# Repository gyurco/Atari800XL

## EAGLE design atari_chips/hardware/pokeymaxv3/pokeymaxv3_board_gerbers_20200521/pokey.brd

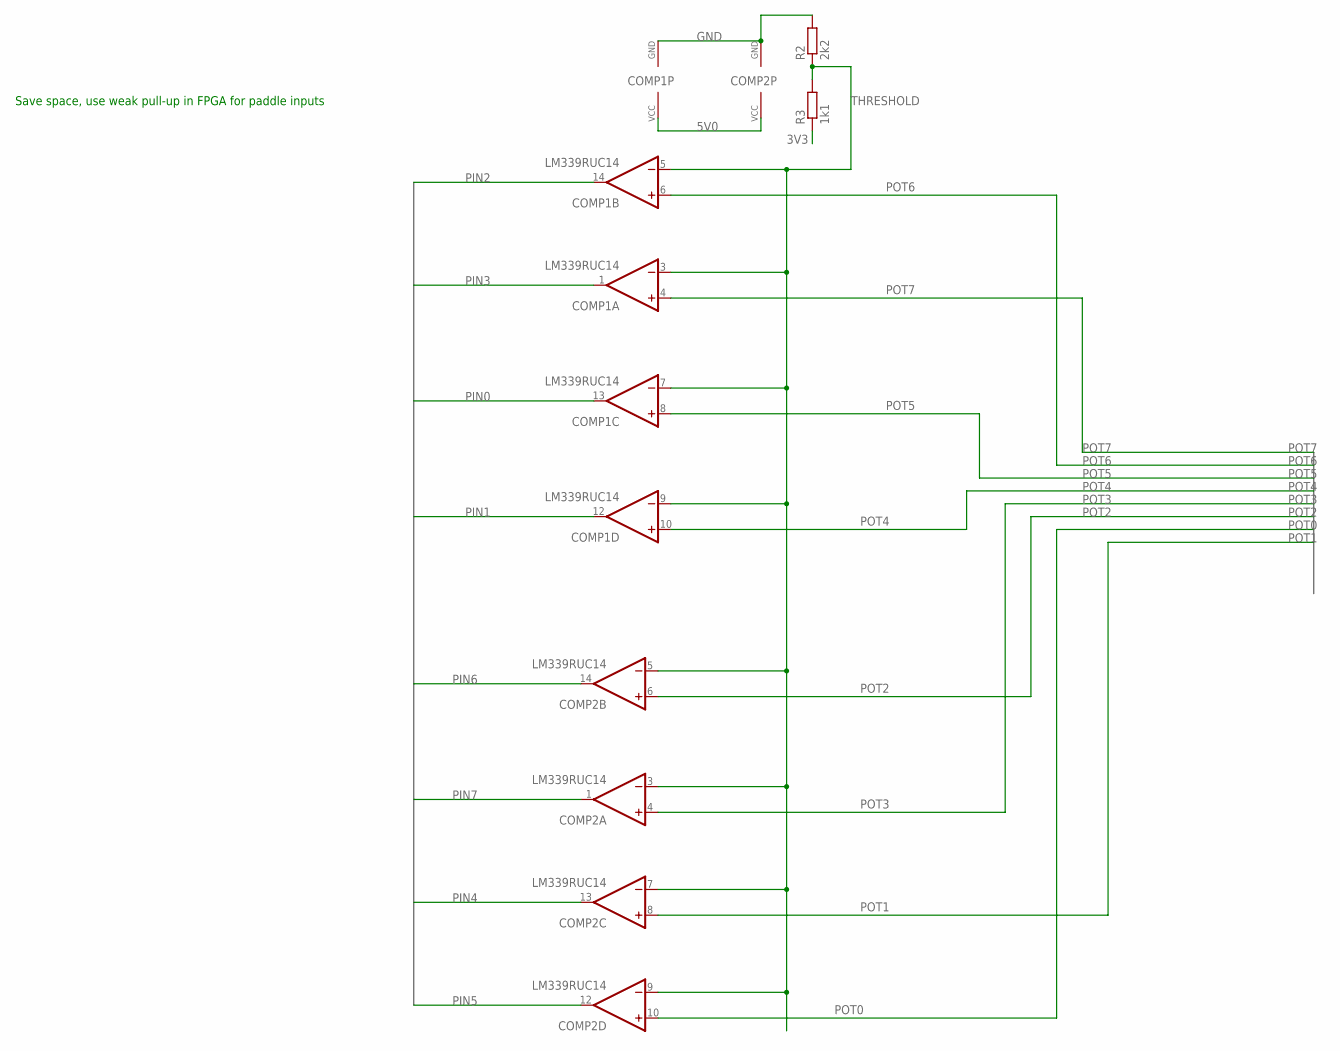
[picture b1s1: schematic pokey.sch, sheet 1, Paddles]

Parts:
COMP1, COMP2: LM339RUC14; RUC14
R2: 2k2; R0402
R3: 1k1; R0402

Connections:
3V3: R3.1; also elsewhere on the board
5V0: COMP1.2 (VCC), COMP2.2 (VCC); also elsewhere on the board
GND: COMP1.11 (GND), COMP2.11 (GND), R2.2; also elsewhere on the board
PIN0: COMP1.13 (OUT); also elsewhere on the board
PIN1: COMP1.12 (OUT); also elsewhere on the board
PIN2: COMP1.14 (OUT); also elsewhere on the board
PIN3: COMP1.1 (OUT); also elsewhere on the board
PIN4: COMP2.13 (OUT); also elsewhere on the board
PIN5: COMP2.12 (OUT); also elsewhere on the board
PIN6: COMP2.14 (OUT); also elsewhere on the board
PIN7: COMP2.1 (OUT); also elsewhere on the board
POT0: COMP2.10 (+IN); also elsewhere on the board
POT1: COMP2.8 (+IN); also elsewhere on the board
POT2: COMP2.6 (+IN); also elsewhere on the board
POT3: COMP2.4 (+IN); also elsewhere on the board
POT4: COMP1.10 (+IN); also elsewhere on the board
POT5: COMP1.8 (+IN); also elsewhere on the board
POT6: COMP1.6 (+IN); also elsewhere on the board
POT7: COMP1.4 (+IN); also elsewhere on the board
THRESHOLD: COMP1.3 (-IN), COMP1.5 (-IN), COMP1.7 (-IN), COMP1.9 (-IN), COMP2.3 (-IN), COMP2.5 (-IN), COMP2.7 (-IN), COMP2.9 (-IN), R2.1, R3.2

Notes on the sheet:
Save space, use weak pull-up in FPGA for paddle inputs

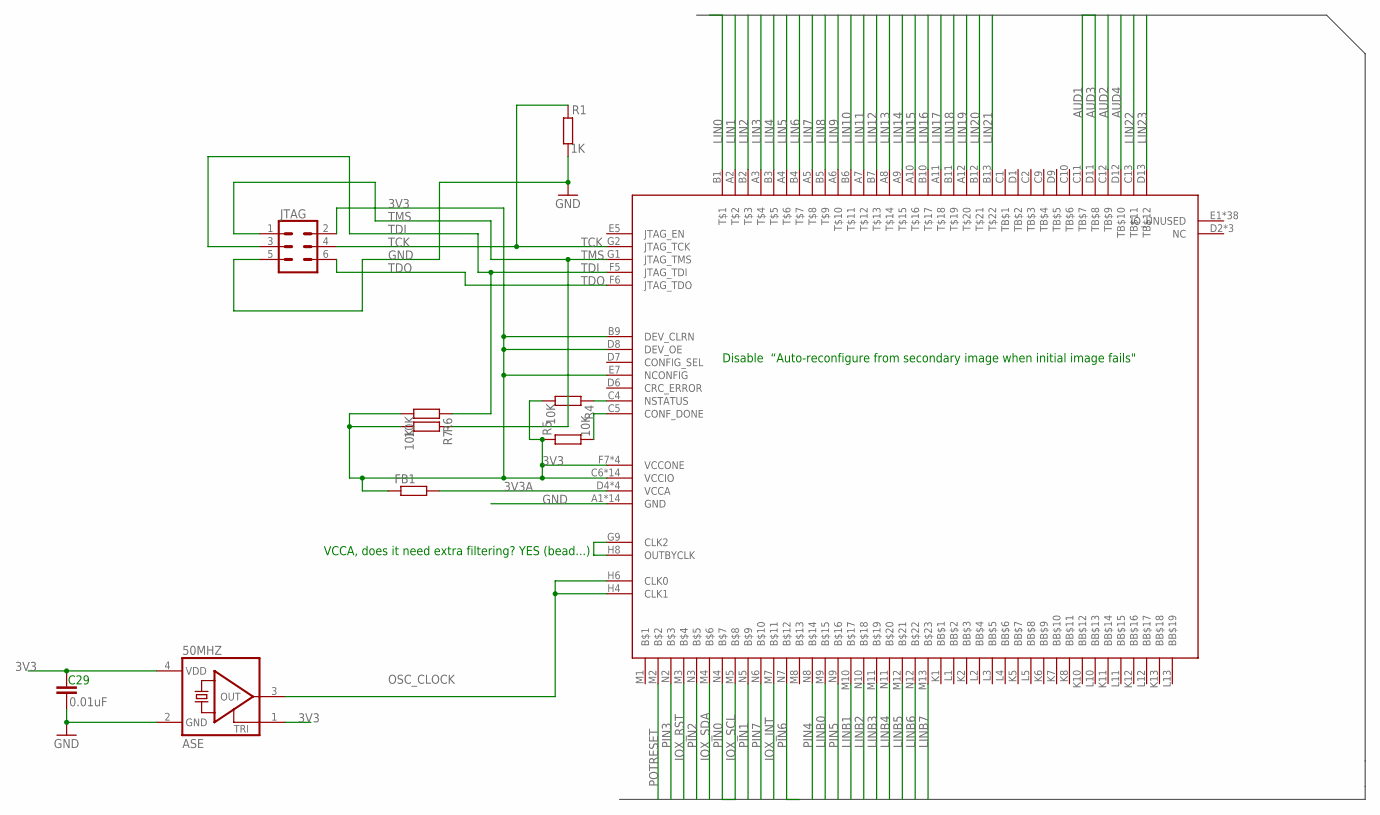
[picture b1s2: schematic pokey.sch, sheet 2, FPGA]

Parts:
50MHZ: ASE
C29: 0.01uF; C0402
FB1: R-EU_R0402; R0402
JTAG: CONN_03X2LOCK; 2X3_LOCK
MAX10: MAX10; U169SMALL
R1: 1K; R0402
R4, R5, R6, R7: 10K; R0402

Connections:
3V3: 50MHZ.1 (TRI), 50MHZ.4 (VDD), C29.1, FB1.1, JTAG.2, MAX10.B9 (DEV_CLRN), MAX10.C6 (VCCIO), MAX10.C7 (VCCIO), MAX10.C8 (VCCIO), MAX10.D8 (DEV_OE), MAX10.E7 (NCONFIG), MAX10.F2 (VCCIO), MAX10.F7 (VCCONE), MAX10.F11 (VCCIO), MAX10.G3 (VCCIO), MAX10.G6 (VCCONE), MAX10.G8 (VCCONE), MAX10.G11 (VCCIO), MAX10.H7 (VCCONE), MAX10.H11 (VCCIO), MAX10.J3 (VCCIO), MAX10.J11 (VCCIO), MAX10.K3 (VCCIO), MAX10.L6 (VCCIO), MAX10.L7 (VCCIO), MAX10.L8 (VCCIO), R4.2, R5.1, R6.2, R7.2; also elsewhere on the board
3V3A: FB1.2, MAX10.D4 (VCCA), MAX10.D10 (VCCA), MAX10.K4 (VCCA), MAX10.K9 (VCCA); also elsewhere on the board
AUD1: MAX10.C11 (TB$7); also elsewhere on the board
AUD2: MAX10.C12 (TB$9); also elsewhere on the board
AUD3: MAX10.D11 (TB$8); also elsewhere on the board
AUD4: MAX10.D12 (TB$10); also elsewhere on the board
CONF_DONE: MAX10.C5 (CONF_DONE), R5.2
FAKE_CLK: MAX10.G9 (CLK2), MAX10.H8 (OUTBYCLK)
GND: 50MHZ.2 (GND), C29.2, JTAG.5, MAX10.A1 (GND), MAX10.A13 (GND), MAX10.B8 (GND), MAX10.C3 (GND), MAX10.D5 (GND), MAX10.E11 (GND), MAX10.F3 (GND), MAX10.G7 (GND), MAX10.H12 (GND), MAX10.J4 (GND), MAX10.L9 (GND), MAX10.M6 (GND), MAX10.N1 (GND), MAX10.N13 (GND), R1.2; also elsewhere on the board
IOX_INT: MAX10.M7; also elsewhere on the board
IOX_RST: MAX10.M3; also elsewhere on the board
IOX_SCL: MAX10.M5; also elsewhere on the board
IOX_SDA: MAX10.M4; also elsewhere on the board
LIN0: MAX10.B1; also elsewhere on the board
LIN1: MAX10.A2; also elsewhere on the board
LIN2: MAX10.B2; also elsewhere on the board
LIN3: MAX10.A3; also elsewhere on the board
LIN4: MAX10.B3; also elsewhere on the board
LIN5: MAX10.A4; also elsewhere on the board
LIN6: MAX10.B4; also elsewhere on the board
LIN7: MAX10.A5; also elsewhere on the board
LIN8: MAX10.B5; also elsewhere on the board
LIN9: MAX10.A6; also elsewhere on the board
LIN10: MAX10.B6; also elsewhere on the board
LIN11: MAX10.A7; also elsewhere on the board
LIN12: MAX10.B7; also elsewhere on the board
LIN13: MAX10.A8; also elsewhere on the board
LIN14: MAX10.A9; also elsewhere on the board
LIN15: MAX10.A10; also elsewhere on the board
LIN16: MAX10.B10; also elsewhere on the board
LIN17: MAX10.A11; also elsewhere on the board
LIN18: MAX10.B11; also elsewhere on the board
LIN19: MAX10.A12; also elsewhere on the board
LIN20: MAX10.B12; also elsewhere on the board
LIN21: MAX10.B13; also elsewhere on the board
LIN22: MAX10.C13 (TB$11); also elsewhere on the board
LIN23: MAX10.D13 (TB$12); also elsewhere on the board
LINB0: MAX10.M9; also elsewhere on the board
LINB1: MAX10.M10; also elsewhere on the board
LINB2: MAX10.N10; also elsewhere on the board
LINB3: MAX10.M11; also elsewhere on the board
LINB4: MAX10.N11; also elsewhere on the board
LINB5: MAX10.M12; also elsewhere on the board
LINB6: MAX10.N12; also elsewhere on the board
LINB7: MAX10.M13; also elsewhere on the board
NSTATUS: MAX10.C4 (NSTATUS), R4.1
OSC_CLOCK: 50MHZ.3 (OUT), MAX10.H4 (CLK1), MAX10.H6 (CLK0)
PIN0: MAX10.N4; also elsewhere on the board
PIN1: MAX10.N5; also elsewhere on the board
PIN2: MAX10.N3; also elsewhere on the board
PIN3: MAX10.N2; also elsewhere on the board
PIN4: MAX10.N8; also elsewhere on the board
PIN5: MAX10.N9; also elsewhere on the board
PIN6: MAX10.N7; also elsewhere on the board
PIN7: MAX10.N6; also elsewhere on the board
POTRESET: MAX10.M2; also elsewhere on the board
TCK: JTAG.4, MAX10.G2 (JTAG_TCK), R1.1
TDI: JTAG.3, MAX10.F5 (JTAG_TDI), R6.1
TDO: JTAG.6, MAX10.F6 (JTAG_TDO)
TMS: JTAG.1, MAX10.G1 (JTAG_TMS), R7.1

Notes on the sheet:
VCCA, does it need extra filtering? YES (bead...)
Disable “Auto-reconfigure from secondary image when initial image fails"

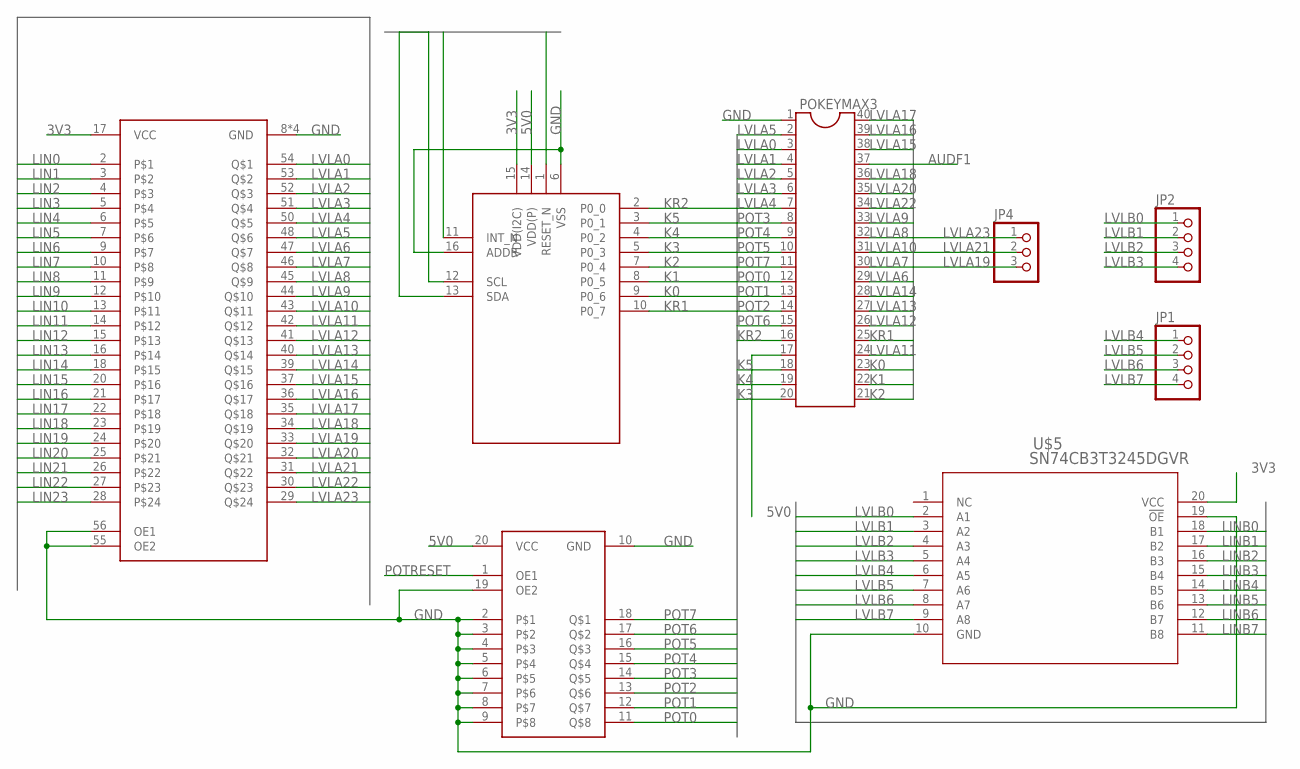
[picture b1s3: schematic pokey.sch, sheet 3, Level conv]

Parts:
JP1, JP2: PINHD-1X4; 1X04
JP4: PINHD-1X3; 1X03
POKEYMAX3: DIL40
U$1: PCAL6408A; XQFN16V2
U$2: SN74CB3T16211; 56TVSOP
U$4: 74AHCT541ADHVQFN-EP; DHVQFN-EP
U$5: SN74CB3T3245DGVR; DGV20

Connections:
3V3: U$1.15 (VDD(I2C)), U$2.17 (VCC), U$5.20 (VCC); also elsewhere on the board
5V0: POKEYMAX3.17, U$1.14 (VDD(P)), U$4.20 (VCC); also elsewhere on the board
AUDF1: POKEYMAX3.37; also elsewhere on the board
GND: POKEYMAX3.1, U$1.6 (VSS), U$1.16 (ADDR), U$2.8 (GND), U$2.19 (GND), U$2.38 (GND), U$2.49 (GND), U$2.55 (OE2), U$2.56 (OE1), U$4.2, U$4.3, U$4.4, U$4.5, U$4.6, U$4.7, U$4.8, U$4.9, U$4.10 (GND), U$4.19 (OE2), U$5.10 (GND), U$5.19 (!OE); also elsewhere on the board
IOX_INT: U$1.11 (INT_N); also elsewhere on the board
IOX_RST: U$1.1 (RESET_N); also elsewhere on the board
IOX_SCL: U$1.12 (SCL); also elsewhere on the board
IOX_SDA: U$1.13 (SDA); also elsewhere on the board
K0: POKEYMAX3.23, U$1.9 (P0_6)
K1: POKEYMAX3.22, U$1.8 (P0_5)
K2: POKEYMAX3.21, U$1.7 (P0_4)
K3: POKEYMAX3.20, U$1.5 (P0_3)
K4: POKEYMAX3.19, U$1.4 (P0_2)
K5: POKEYMAX3.18, U$1.3 (P0_1)
KR1: POKEYMAX3.25, U$1.10 (P0_7)
KR2: POKEYMAX3.16, U$1.2 (P0_0)
LIN0: U$2.2; also elsewhere on the board
LIN1: U$2.3; also elsewhere on the board
LIN2: U$2.4; also elsewhere on the board
LIN3: U$2.5; also elsewhere on the board
LIN4: U$2.6; also elsewhere on the board
LIN5: U$2.7; also elsewhere on the board
LIN6: U$2.9; also elsewhere on the board
LIN7: U$2.10; also elsewhere on the board
LIN8: U$2.11; also elsewhere on the board
LIN9: U$2.12; also elsewhere on the board
LIN10: U$2.13; also elsewhere on the board
LIN11: U$2.14; also elsewhere on the board
LIN12: U$2.15; also elsewhere on the board
LIN13: U$2.16; also elsewhere on the board
LIN14: U$2.18; also elsewhere on the board
LIN15: U$2.20; also elsewhere on the board
LIN16: U$2.21; also elsewhere on the board
LIN17: U$2.22; also elsewhere on the board
LIN18: U$2.23; also elsewhere on the board
LIN19: U$2.24; also elsewhere on the board
LIN20: U$2.25; also elsewhere on the board
LIN21: U$2.26; also elsewhere on the board
LIN22: U$2.27; also elsewhere on the board
LIN23: U$2.28; also elsewhere on the board
LINB0: U$5.18 (B1); also elsewhere on the board
LINB1: U$5.17 (B2); also elsewhere on the board
LINB2: U$5.16 (B3); also elsewhere on the board
LINB3: U$5.15 (B4); also elsewhere on the board
LINB4: U$5.14 (B5); also elsewhere on the board
LINB5: U$5.13 (B6); also elsewhere on the board
LINB6: U$5.12 (B7); also elsewhere on the board
LINB7: U$5.11 (B8); also elsewhere on the board
LVLA0: POKEYMAX3.3, U$2.54
LVLA1: POKEYMAX3.4, U$2.53
LVLA2: POKEYMAX3.5, U$2.52
LVLA3: POKEYMAX3.6, U$2.51
LVLA4: POKEYMAX3.7, U$2.50
LVLA5: POKEYMAX3.2, U$2.48
LVLA6: POKEYMAX3.29, U$2.47
LVLA7: POKEYMAX3.30, U$2.46
LVLA8: POKEYMAX3.32, U$2.45
LVLA9: POKEYMAX3.33, U$2.44
LVLA10: POKEYMAX3.31, U$2.43
LVLA11: POKEYMAX3.24, U$2.42
LVLA12: POKEYMAX3.26, U$2.41
LVLA13: POKEYMAX3.27, U$2.40
LVLA14: POKEYMAX3.28, U$2.39
LVLA15: POKEYMAX3.38, U$2.37
LVLA16: POKEYMAX3.39, U$2.36
LVLA17: POKEYMAX3.40, U$2.35
LVLA18: POKEYMAX3.36, U$2.34
LVLA19: JP4.3, U$2.33
LVLA20: POKEYMAX3.35, U$2.32
LVLA21: JP4.2, U$2.31
LVLA22: POKEYMAX3.34, U$2.30
LVLA23: JP4.1, U$2.29
LVLB0: JP2.1, U$5.2 (A1)
LVLB1: JP2.2, U$5.3 (A2)
LVLB2: JP2.3, U$5.4 (A3)
LVLB3: JP2.4, U$5.5 (A4)
LVLB4: JP1.1, U$5.6 (A5)
LVLB5: JP1.2, U$5.7 (A6)
LVLB6: JP1.3, U$5.8 (A7)
LVLB7: JP1.4, U$5.9 (A8)
POT0: POKEYMAX3.12, U$4.11; also elsewhere on the board
POT1: POKEYMAX3.13, U$4.12; also elsewhere on the board
POT2: POKEYMAX3.14, U$4.13; also elsewhere on the board
POT3: POKEYMAX3.8, U$4.14; also elsewhere on the board
POT4: POKEYMAX3.9, U$4.15; also elsewhere on the board
POT5: POKEYMAX3.10, U$4.16; also elsewhere on the board
POT6: POKEYMAX3.15, U$4.17; also elsewhere on the board
POT7: POKEYMAX3.11, U$4.18; also elsewhere on the board
POTRESET: U$4.1 (OE1); also elsewhere on the board

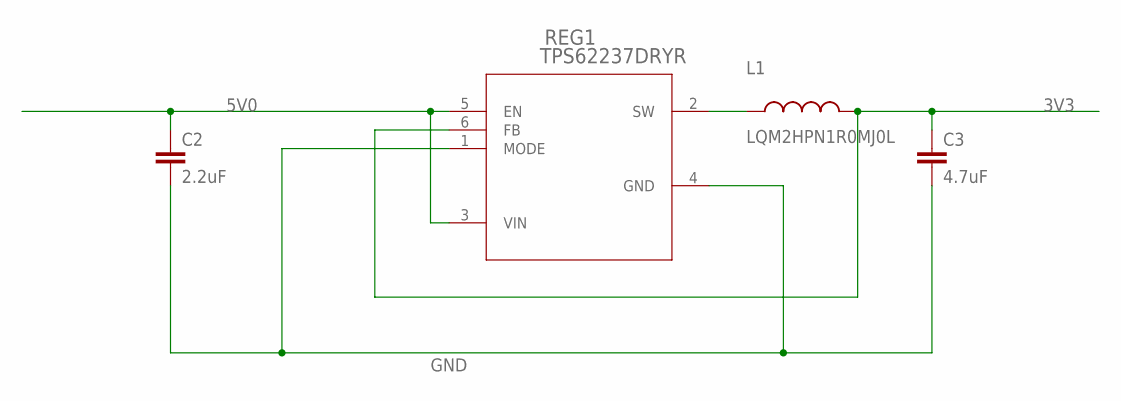
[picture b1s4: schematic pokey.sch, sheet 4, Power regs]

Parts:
C2: 2.2uF; C0402
C3: 4.7uF; C0402
L1: LQM2HPN1R0MJ0L; INDC1008X04
REG1: TPS62237DRYR; DRY6

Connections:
3V3: C3.1, L1.2, REG1.6 (FB); also elsewhere on the board
5V0: C2.1, REG1.3 (VIN), REG1.5 (EN); also elsewhere on the board
GND: C2.2, C3.2, REG1.1 (MODE), REG1.4 (GND); also elsewhere on the board
unnamed: L1.1, REG1.2 (SW)

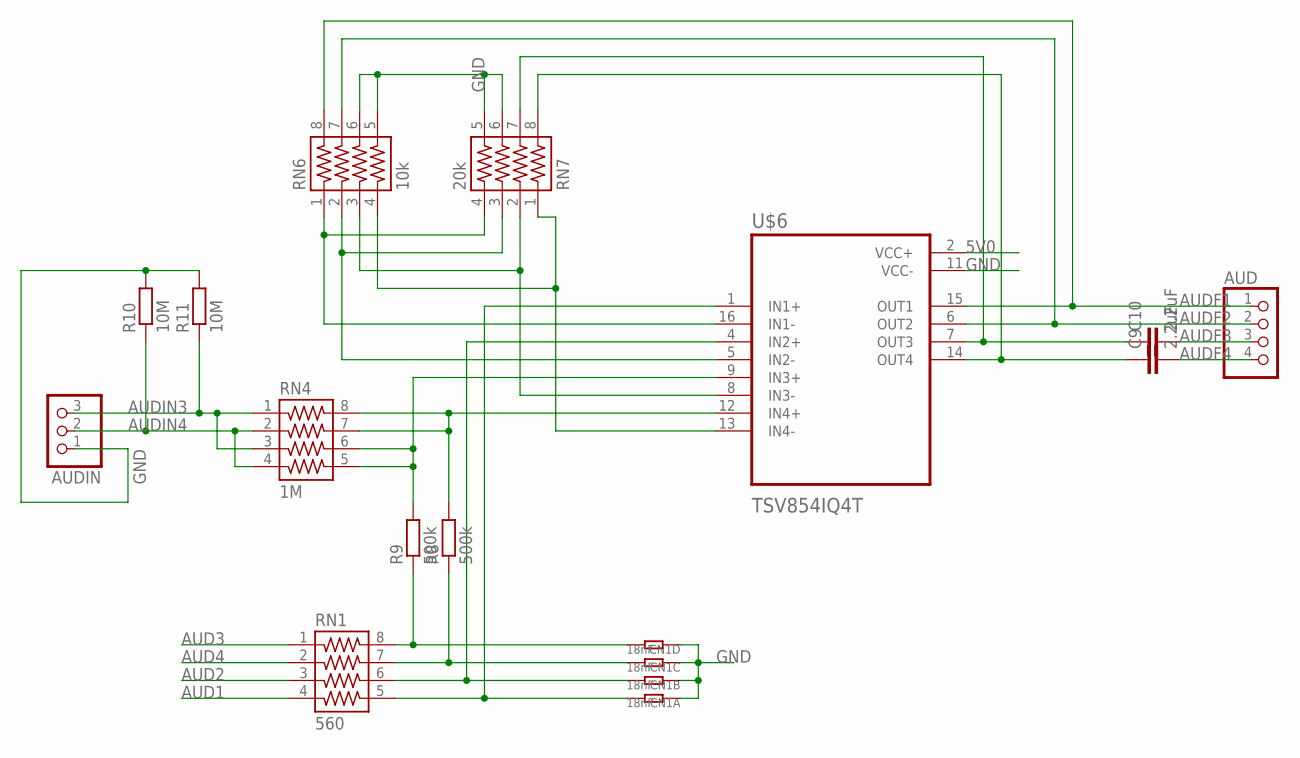
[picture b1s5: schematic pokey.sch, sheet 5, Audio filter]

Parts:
AUD: PINHD-1X4; 1X04
AUDIN: PINHD-1X3; 1X03
C9, C10: 2.2uF; C0402
CN1: 18nF; R1206-8
R8, R9: 500k; R0402
R10, R11: 10M; R0402
RN1: 560; 742-8
RN4: 1M; 742-8
RN6: 10k; 742-8
RN7: 20k; 742-8
U$6: TSV854IQ4T; QFN50P300X300X100-16N

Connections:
5V0: U$6.2 (VCC+); also elsewhere on the board
AMPIN1M: RN6.1, RN7.4, U$6.16 (IN1-)
AMPIN1P: CN1.8 (2), RN1.5, U$6.1 (IN1+)
AMPIN2M: RN6.2, RN7.3, U$6.5 (IN2-)
AMPIN2P: CN1.7 (2), RN1.6, U$6.4 (IN2+)
AMPIN3M: RN6.3, RN7.2, U$6.8 (IN3-)
AMPIN3P: R9.2, RN4.5, RN4.6, U$6.9 (IN3+)
AMPIN4P: R8.2, RN4.7, RN4.8, U$6.12 (IN4+)
AUD1: RN1.4; also elsewhere on the board
AUD2: RN1.3; also elsewhere on the board
AUD3: RN1.1; also elsewhere on the board
AUD4: RN1.2; also elsewhere on the board
AUDF1: AUD.1, RN6.8, U$6.15 (OUT1); also elsewhere on the board
AUDF2: AUD.2, RN6.7, U$6.6 (OUT2)
AUDF3: AUD.3, C10.2
AUDF4: AUD.4, C9.2
AUDIN3: AUDIN.3, R11.1, RN4.1, RN4.3
AUDIN4: AUDIN.2, R10.1, RN4.2, RN4.4
GND: AUDIN.1, CN1.1, CN1.2 (1), CN1.3 (1), CN1.4 (1), R10.2, R11.2, RN6.5, RN6.6, RN7.5, RN7.6, U$6.11 (VCC-); also elsewhere on the board
unnamed: CN1.5 (2), R9.1, RN1.8
unnamed: CN1.6 (2), R8.1, RN1.7
unnamed: C9.1, RN7.8, U$6.14 (OUT4)
unnamed: C10.1, RN7.7, U$6.7 (OUT3)
unnamed: RN6.4, RN7.1, U$6.13 (IN4-)

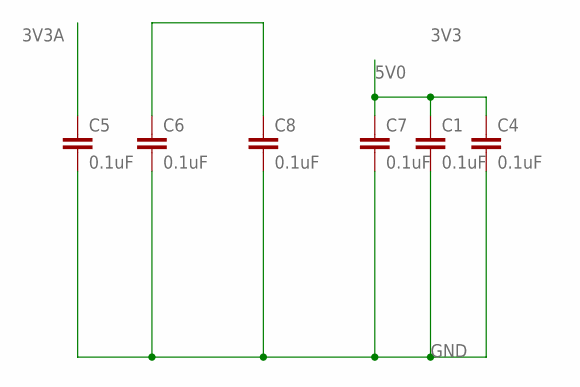
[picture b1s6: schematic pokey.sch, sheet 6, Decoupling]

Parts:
C1, C4, C5, C6, C7, C8: 0.1uF; C0402

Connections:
3V3: C6.1, C8.1; also elsewhere on the board
3V3A: C5.1; also elsewhere on the board
5V0: C1.1, C4.1, C7.1; also elsewhere on the board
GND: C1.2, C4.2, C5.2, C6.2, C7.2, C8.2; also elsewhere on the board

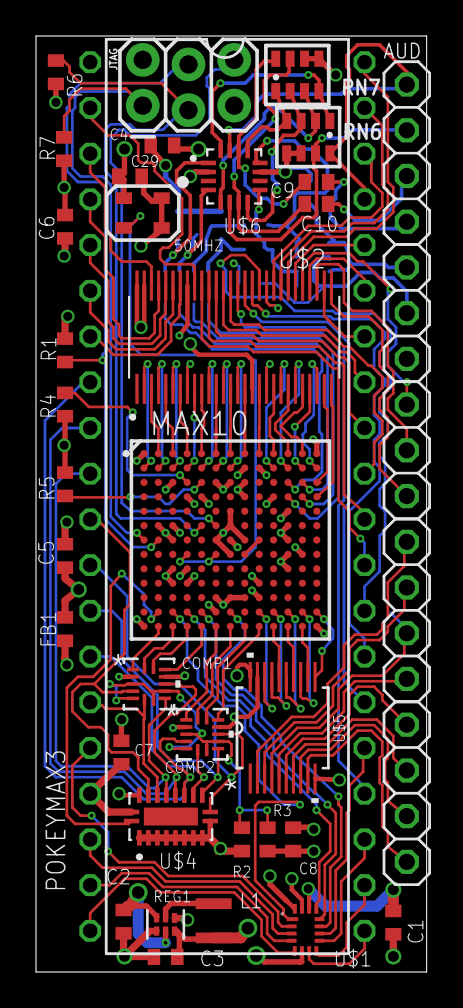
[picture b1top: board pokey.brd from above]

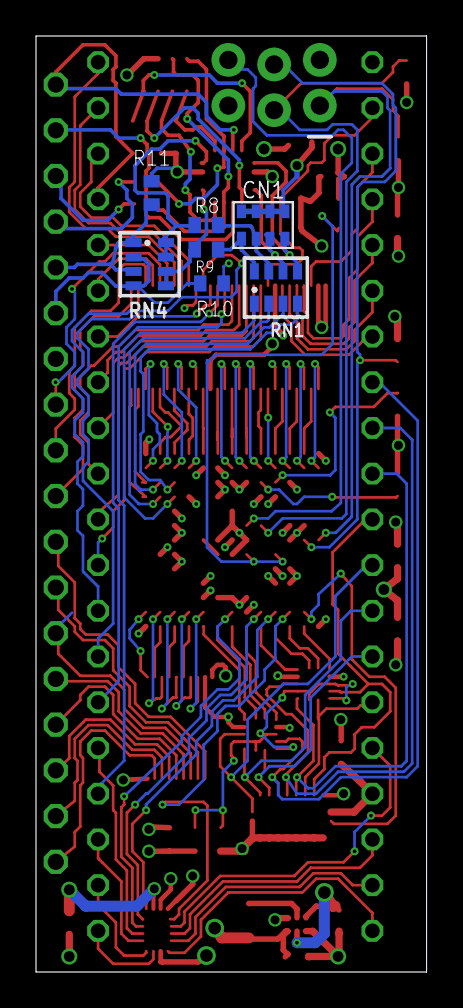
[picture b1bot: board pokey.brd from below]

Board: 4 copper layers, 21.7 x 52.0 mm, 46 parts (7 on the bottom side), 129 nets.

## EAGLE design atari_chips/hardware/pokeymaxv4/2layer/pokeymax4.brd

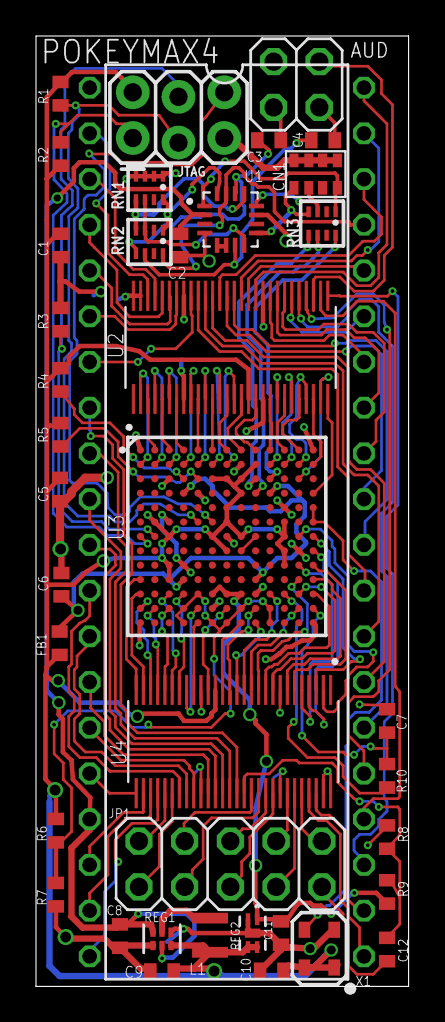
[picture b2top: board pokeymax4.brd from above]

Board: 4 copper layers, 20.7 x 52.8 mm, 39 parts (0 on the bottom side), 129 nets.

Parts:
AUD: 2X02
C1, C2, C5, C6, C11: 0.1uF; C0402
C3, C4, C8, C12: 2.2uF; C0402
C7: 1nF; C0402
C9: 4.7uF; C0402
C10: 0.01uF; C0402
CN1: 18nF; R1206-8
FB1: R0402
JP1: 2X05
JTAG: 2X3_LOCK
L1: LQM2HPN1R0MJ0L; INDC1008X04
POKEYMAX4: DIL40
R1, R2, R4, R5: 10K; R0402
R3: 1K; R0402
R6, R10: 1k1; R0402
R7: 2k2; R0402
R8, R9: 3k3; R0402
REG1: TPS62237DRYR; DRY6
REG2: MIC94310-JYMT-TR; TDFN4_1P2X1P6_MCH
RN1: 20K; 741-8
RN2: 10K; 741-8
RN3: 560; 741-8
U1: TSV854IQ4T; QFN50P300X300X100-16N
U2, U4: SN74CB3T16211SM; 56TVSOP_SMALL
U3: MAX10; U169SMALL
X1: ASE

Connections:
2V5: C11.1, R9.2, REG2.1, U3.L6, U3.L7, U3.L8
3V3: C1.1, C5.1, C9.1, C10.1, FB1.1, JTAG.2, L1.2, R1.2, R2.2, R4.2, R5.1, R6.2, REG1.6, REG2.3, REG2.4, U2.17, U3.B9, U3.C6, U3.C7, U3.C8, U3.D8, U3.E7, U3.F2, U3.F7, U3.F11, U3.G3, U3.G6, U3.G8, U3.G11, U3.H7, U3.H11, U3.J3, U3.J11, U3.K3, U4.17, X1.1, X1.4
3V3A: C6.1, FB1.2, U3.D4, U3.D10, U3.K4, U3.K9
5V0: C2.1, C8.1, POKEYMAX4.17, REG1.3, REG1.5, U1.2
ADC_RX: C7.1, R10.2, U3.M13
ADC_TX: R10.1, U3.L11
AMPIN1M: RN1.8, RN2.1, U1.16
AMPIN1P: CN1.8, RN3.1, U1.1
AMPIN3M: RN1.6, RN2.3, U1.8
AMPIN3P: CN1.5, RN3.4, U1.9
AMPIN4P: CN1.6, RN3.3, U1.12
AUD1: RN3.8, U3.C10
AUD3: RN3.5, U3.C9
AUD4: RN3.6, U3.D9
AUDF1: POKEYMAX4.37, RN2.8, U1.15
AUDF2: U1.5, U1.6
AUDF3: AUD.3, C4.2
AUDF4: AUD.1, C3.2
AUD_IN: C12.2, JP1.9
CONF_DONE: R5.2, U3.C5
FAKE_CLK: U3.G9, U3.H8
GND: AUD.2, C1.2, C2.2, C5.2, C6.2, C7.2, C8.2, C9.2, C10.2, C11.2, CN1.1, CN1.2, CN1.3, CN1.4, JTAG.5, POKEYMAX4.1, R3.2, R7.1, R8.1, REG1.1, REG1.4, REG2.2, REG2.5, RN1.1, RN1.2, RN1.3, RN1.4, U1.4, U1.11, U2.8, U2.19, U2.38, U2.49, U2.55, U2.56, U3.A1, U3.A13, U3.B8, U3.C3, U3.D5, U3.E11, U3.F3, U3.G7, U3.H12, U3.J4, U3.L9, U3.M6, U3.N1, U3.N13, U4.8, U4.19, U4.38, U4.49, U4.55, U4.56, X1.2
LIN0: U2.2, U3.B1
LIN1: U2.3, U3.A2
LIN2: U2.4, U3.B2
LIN3: U2.5, U3.A3
LIN4: U2.6, U3.B3
LIN5: U2.7, U3.A4
LIN6: U2.9, U3.B4
LIN7: U2.10, U3.A5
LIN8: U2.11, U3.B5
LIN9: U2.12, U3.A6
LIN10: U2.13, U3.B6
LIN11: U2.14, U3.A7
LIN12: U2.15, U3.B7
LIN13: U2.16, U3.A8
LIN14: U2.18, U3.A9
LIN15: U2.20, U3.A10
LIN16: U2.21, U3.B10
LIN17: U2.22, U3.A11
LIN18: U2.23, U3.B11
LIN19: U2.24, U3.A12
LIN20: U2.25, U3.B12
LIN21: U2.26, U3.B13
LIN22: U2.27, U3.C12
LIN23: U2.28, U3.D13
LINB0: U3.G12, U4.2
LINB1: U3.G13, U4.3
LINB2: U3.H13, U4.4
LINB3: U3.J12, U4.5
LINB4: U3.J13, U4.6
LINB5: U3.K13, U4.7
LINB6: U3.L12, U4.9
LINB7: U3.L13, U4.10
LINB8: U3.K12, U4.11
LINB9: U3.M12, U4.12
LINB10: U3.L10, U4.13
LINB11: U3.N9, U4.14
LINB12: U3.M9, U4.15
LINB13: U3.N8, U4.16
LINB14: U3.M7, U4.18
LINB15: U3.N5, U4.20
LINB16: U3.M5, U4.21
LINB17: U3.L4, U4.22
LINB18: U3.L3, U4.23
LINB19: U3.M3, U4.24
LINB20: U3.M2, U4.25
LINB21: U3.M1, U4.26
LINB22: U3.L1, U4.27
LINB23: U3.K1, U4.28
LVLA0: POKEYMAX4.2, U2.54
LVLA1: POKEYMAX4.3, U2.53
LVLA2: POKEYMAX4.4, U2.52
LVLA3: POKEYMAX4.5, U2.51
LVLA4: POKEYMAX4.6, U2.50
LVLA5: POKEYMAX4.7, U2.48
LVLA6: POKEYMAX4.29, U2.47
LVLA7: POKEYMAX4.28, U2.46
LVLA8: POKEYMAX4.27, U2.45
LVLA9: POKEYMAX4.38, U2.44
LVLA10: POKEYMAX4.31, U2.43
LVLA11: POKEYMAX4.30, U2.42
LVLA12: POKEYMAX4.39, U2.41
LVLA13: POKEYMAX4.36, U2.40
LVLA14: POKEYMAX4.40, U2.39
LVLA15: POKEYMAX4.34, U2.37
LVLA16: POKEYMAX4.33, U2.36
LVLA17: POKEYMAX4.32, U2.35
LVLA18: POKEYMAX4.35, U2.34
LVLA19: POKEYMAX4.26, U2.33
LVLA20: POKEYMAX4.25, U2.32
LVLA21: AUD.4, U2.31
LVLA22: POKEYMAX4.24, U2.30
LVLA23: POKEYMAX4.23, U2.29
LVLB0: POKEYMAX4.22, U4.54
LVLB1: POKEYMAX4.21, U4.53
LVLB2: JP1.10, U4.52
LVLB3: JP1.7, U4.51
LVLB4: JP1.8, U4.50
LVLB5: JP1.5, U4.48
LVLB6: JP1.6, U4.47
LVLB7: JP1.3, U4.46
LVLB8: JP1.4, U4.45
LVLB9: C12.1, R8.2, R9.1, U4.44
LVLB10: POKEYMAX4.8, U4.43
LVLB11: POKEYMAX4.9, U4.42
LVLB12: POKEYMAX4.10, U4.41
LVLB13: POKEYMAX4.11, U4.40
LVLB14: POKEYMAX4.14, U4.39
LVLB15: POKEYMAX4.15, U4.37
LVLB16: POKEYMAX4.13, U4.36
LVLB17: POKEYMAX4.12, U4.35
LVLB18: JP1.1, U4.34
LVLB19: JP1.2, U4.33
LVLB20: POKEYMAX4.20, U4.32
LVLB21: POKEYMAX4.19, U4.31
LVLB22: POKEYMAX4.18, U4.30
LVLB23: POKEYMAX4.16, U4.29
unnamed: C3.1, RN2.5, U1.14
unnamed: C4.1, RN2.6, U1.7
unnamed: RN1.5, RN2.4, U1.13
unnamed: L1.1, REG1.2
NSTATUS: R4.1, U3.C4
OSC_CLOCK: U3.E13, U3.F13, X1.3
PTHRES: R6.1, R7.2, U3.L5, U3.M4, U3.M8, U3.M10, U3.N4, U3.N6, U3.N7, U3.N10
TCK: JTAG.4, R3.1, U3.G2
TDI: JTAG.3, R1.1, U3.F5
TDO: JTAG.6, U3.F6
TMS: JTAG.1, R2.1, U3.G1

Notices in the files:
eclaireXL/hardware/eagle_projects/cart_pbi_breakout/de1_breakout.brd:
(c) 2015 Mark Watson and Matthias Reichl
eclaireXL/hardware/eagle_projects/mainboard/atari_superxe_motherboard.brd:
(c)2016
parts and their libraries:
resistor-array: Copyright (C) 2008, Bob Starr
SparkFun-Connectors: Licensing: Creative Commons ShareAlike 4.0 International - https://creativecommons.org/licenses/by-sa/4.0
COPYRIGHT: Copyright (C) 2018 Accelerated Designs. All rights reserved
atari: Copyright (c) 2010
Copyright (c) 2009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
